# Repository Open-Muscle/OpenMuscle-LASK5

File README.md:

# LASK5 – A Gloveless Smart Glove Controller

LASK5 is a compact, gloveless smart glove controller designed for robotics, machine learning, and human-computer interaction projects. Originally created to assist with labeling movement data for the [OpenMuscle](https://openmuscle.org) project, this controller is now a fully open-source interface capable of controlling robotic hands, LED sculptures, and more.

```markdown
📌 This device is part of the OpenMuscle ecosystem.  
For project-wide documentation, visit the [OpenMuscle Hub](https://github.com/Open-Muscle/OpenMuscle-Hub).
```

---

## 📽️ Watch the Demo

🎥 **YouTube Video:** [LASK5: The Gloveless Smart Glove](https://youtu.be/DJxaf0ww6us)

---

## 🔧 Features

- ESP32-S3 based (Wi-Fi + ESP-NOW enabled)
- 4-piston finger input with hall sensors
- Thumb joystick
- 128x32 OLED display for menus and feedback
- 4 SMD buttons for UI control
- Modular headers for add-ons (gyroscope, additional sensors)
- Written in MicroPython
- 3D-printable enclosure

---

## 🗂️ Repository Structure

### 🛠️ Hardware (KiCad)

You can find all historical and current KiCad hardware designs under:

📂 [`KiCad/`](https://github.com/Open-Muscle/OpenMuscle-LASK5/tree/main/KiCad)

Each folder contains complete KiCad files, BOMs, and version-specific layout changes.

| Version | Description | Folder |
|---------|-------------|--------|
| **v3.0** (Proposed) | New layout with joystick, button updates | [LASK_V3-0](https://github.com/Open-Muscle/OpenMuscle-LASK5/tree/main/KiCad/LASK_V3-0) |
| v2.0 | Button layout revision, early joystick test | [LASK_V2-0](https://github.com/Open-Muscle/OpenMuscle-LASK5/tree/main/KiCad/LASK_V2-0) |
| v1.1 | Original layout with 3-button config | [LASK_V1-1](https://github.com/Open-Muscle/OpenMuscle-LASK5/tree/main/KiCad/LASK_V1-1) |

🧩 Component footprints are stored in:
- [`ESP32WROOMfootprint`](https://github.com/Open-Muscle/OpenMuscle-LASK5/tree/main/KiCad/ESP32WROOMfootprint)
- [`USBfootprint`](https://github.com/Open-Muscle/OpenMuscle-LASK5/tree/main/KiCad/USBfootprint)
- [`ICM-42688-P`](https://github.com/Open-Muscle/OpenMuscle-LASK5/tree/main/KiCad/ICM-42688-P)

---

### 💾 Firmware

The firmware for all LASK versions is maintained centrally in:

📂 [OpenMuscle-Software → `/embedded/lask5`](https://github.com/Open-Muscle/OpenMuscle-Software/tree/main/embedded/LASK5)

> ✅ Be sure to match the firmware branch or directory with your hardware version (see notes in the firmware repo for version compatibility).

---

## 🧠 Use Cases

- Robotic hand control (e.g. HiWonder, Arduino-powered systems)
- LED and kinetic art control
- Machine learning data labeling (OpenMuscle)
- Custom HCI devices, VR/AR control experiments

---

## 🚀 Getting Started

1. Visit the [OpenMuscle Hub](https://github.com/Open-Muscle/OpenMuscle-Hub) for device setup overview.
2. Select your hardware version from the `/KiCad` folder.
3. Follow included assembly instructions (or upcoming guides at [openmuscle.org](https://openmuscle.org)).
4. Flash your ESP32-S3 using the LASK5 firmware from [OpenMuscle-Software](https://github.com/Open-Muscle/OpenMuscle-Software).
5. Power on, test input, and begin using ESP-NOW or serial modes.

---

## 🤝 Contribute

We welcome PRs for hardware, firmware, or documentation.  
You can also submit ideas or questions in [OpenMuscle Discussions](https://github.com/Open-Muscle/OpenMuscle-Hub/discussions) (coming soon).

> If you build your own LASK5 device, let us know!  
> Tag [@OpenMuscle](https://github.com/Open-Muscle) or submit to the Community Builds section.

---

## 📜 License

This repository is covered by a combination of licenses based on content type:

- **Hardware Design Files** (KiCad schematics, PCB layouts, mechanical files):  
  📄 [CERN Open Hardware License v2.0 – Strongly Reciprocal (CERN-OHL-S)](https://ohwr.org/cern_ohl_s_v2.txt)  
  → You may copy, modify, and manufacture hardware as long as you release modifications under the same license.

- **Firmware and Code Snippets** (e.g. MicroPython, setup scripts):  
  📄 [MIT License](https://opensource.org/licenses/MIT)  
  → You may use, modify, and redistribute the code freely with attribution.

- **Art and Visual Media** (e.g. logos, SVGs, diagrams, illustrations):  
  🎨 [Creative Commons Attribution 4.0 International (CC BY 4.0)](https://creativecommons.org/licenses/by/4.0/)  
  → You may use and remix art assets with credit to the original authors.
  
🔍 The hardware license text lives at [LICENSE](LICENSE) (root) and in [LICENSES/](LICENSES/).

---

Made with 💡 by [TURFPTAx](https://github.com/turfptax) for the OpenMuscle initiative.

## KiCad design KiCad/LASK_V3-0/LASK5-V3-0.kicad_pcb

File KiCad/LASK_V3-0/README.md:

# LASK v3 – OpenMuscle Labeler PCB

**Version:** 3.0  
**KiCad Version:** 9.0.1  
**Project Type:** Embedded hardware (ESP32-based controller)  
**Use Case:** Labeling hand movement data for prosthetic machine learning models

This is the third iteration of the LASK (Labeler for Sensor Kit) PCB, designed as part of the OpenMuscle project. LASK v3 is a handheld device used to interact with muscle sensors, label data, and provide haptic and motion feedback during training sessions.

---

## 🧠 Major Additions in v3

- ✅ Added **haptic motor driver** with flyback diode protection  
- ✅ Added **ICM-42688-P IMU** (I²C, with alternate support for SPI)  
- ✅ Enhanced **power management** using a push-button latch and USB auto-power-on  
- ✅ Clean GPIO assignments for consistent firmware development

---

## 🧩 System Overview

| Subsystem           | Description |
|--------------------|-------------|
| **MCU**            | ESP32-S3-WROOM-1 (16MB flash, 8MB PSRAM) |
| **Sensors**        | 4x Hall effect sensors w/ 100nF capacitors to ground |
| **IMU**            | ICM-42688-P (I²C: GPIO8=SDA, GPIO9=SCL) |
| **Display**        | SSD1306 OLED (I²C shared) |
| **Input**          | 2 buttons (Menu & Select), Thumb joystick w/ push |
| **Output**         | Haptic motor driven via MOSFET on GPIO17 |
| **Power**          | MAX16054 latch, TPS7A0333 LDO, LTC4054 charger |
| **Interface**      | USB-C for charging and programming |

---

## 🧷 GPIO Pinout

| Function                | GPIO |
|------------------------|------|
| Hall Sensor 0          | 1    |
| Hall Sensor 1          | 2    |
| Hall Sensor 2          | 3    |
| Hall Sensor 3          | 4    |
| Joystick X             | 5    |
| Joystick Y             | 6    |
| Joystick Switch        | 7    |
| I²C SDA (IMU + OLED)   | 8    |
| I²C SCL (IMU + OLED)   | 9    |
| Select Button          | 10   |
| SPI MISO               | 11   |
| SPI SCK                | 12   |
| SPI MOSI               | 13   |
| Haptic Motor Signal    | 17   |
| Battery Voltage ADC    | 18   |
| Menu Button            | 21   |
| SPI CS (available)     | 22   |

---

## 🔋 Power Management

- **Charging:** LTC4054 linear charger via USB-C  
- **Voltage Regulation:** TPS7A0333 LDO with EN pin control  
- **Power-on Logic:** MAX16054 handles push-button latching  
  - **VBUS detection** auto-enables LDO via diode OR circuit  
  - Power can also be toggled with push button  
- **Haptic Driver:** IRLML2060 N-MOSFET, protected by 1N4007 diode

---

## 🛠️ Schematic

> 📁 Located in `/kicad_project/`

---

## 🧪 Development Notes

- Future version may migrate IMU to SPI for better performance
- USB VBUS is sensed to allow automatic boot when plugged in
- Add decoupling capacitors on IMU pins for improved stability (see TODO in schematic)

---

## 📂 Repository Structure

```
/
├── kicad_project/
│ ├── LASKS-V3_0.kicad_sch
│ └── LASKS-V3_0.kicad_pcb
├── docs/
│ └── lask_v3_schematic.png
├── README.md
```

---

## 🔓 License

Open-source under [CERN-OHL-W v2](https://ohwr.org/project/cernohl/wikis/CERN-OHL-version-2)  
Part of the [OpenMuscle Project](https://openmuscle.org)

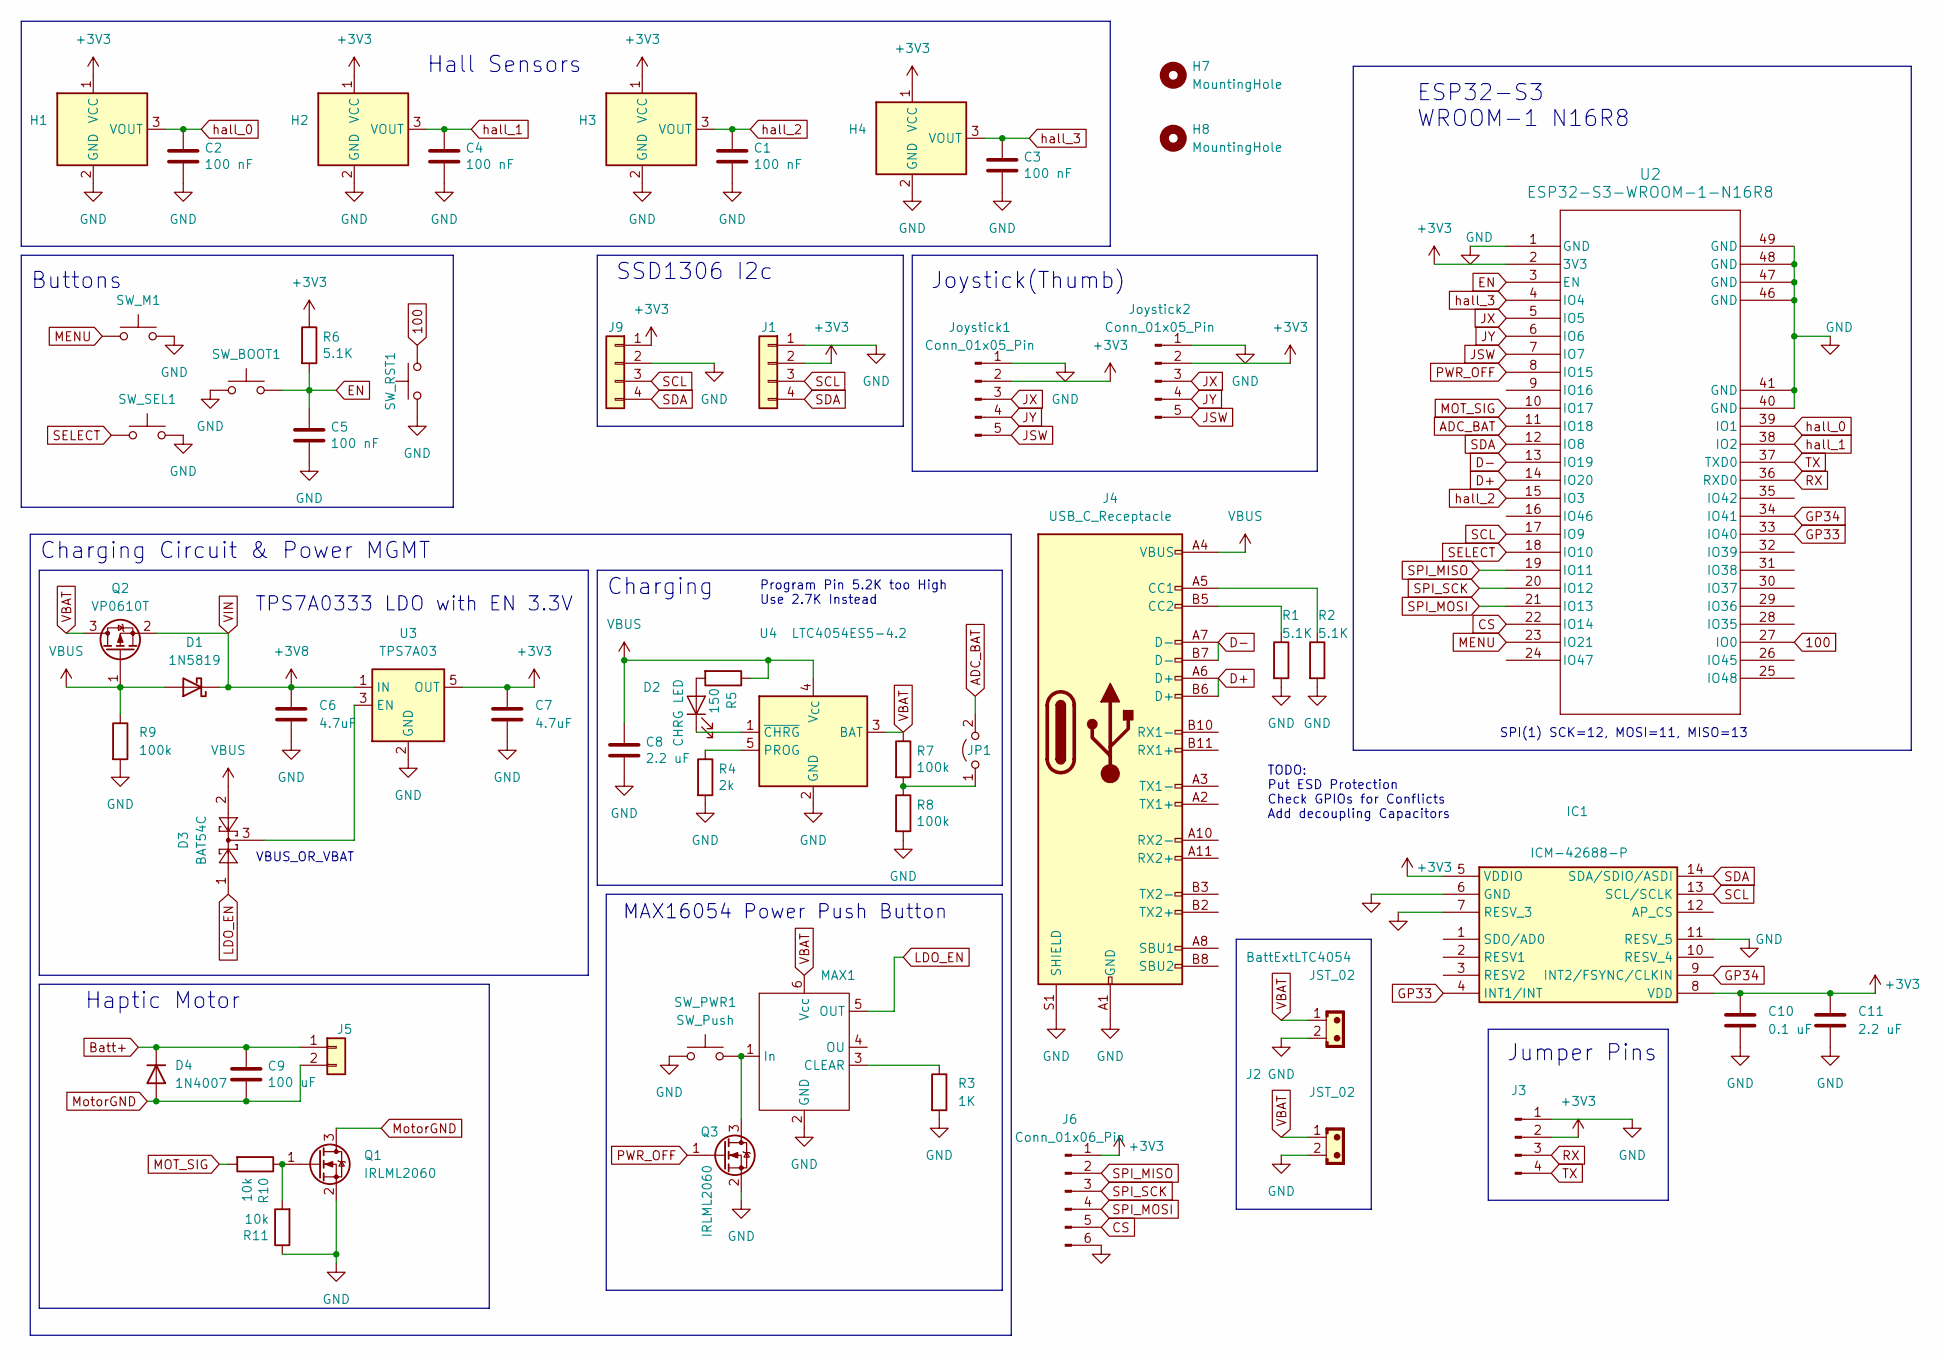
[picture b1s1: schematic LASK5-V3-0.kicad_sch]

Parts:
BattExtLTC4054: JST_02; JST_EH_B2B-EH-A_1x02_P2.50mm_Vertical
C1, C2, C3, C4, C5: 100 nF; C_0603_1608Metric; JLCPN C1525
C6, C7: 4.7uF; C_0805_2012Metric
C8: 2.2 uF; C_0603_1608Metric; JLCPN C12530
C9: 100 uF; C_0603_1608Metric; JLCPN C12530
C10: 0.1 uF; C_0603_1608Metric
C11: 2.2 uF; C_0603_1608Metric
D1: 1N5819; D_SOD-123F
D2: CHRG LED; LED_0805_2012Metric; JLCPN C72043
D3: BAT54C; SOT-23
D4: 1N4007; D_SOD-123
H1, H2, H3, H4: A1369xUA-10; PinHeader_1x03_P2.00mm_Vertical
H7, H8: MountingHole; MountingHole_2.2mm_M2
IC1: ICM-42688-P; IIM42352; Mouser Part Number 410-ICM-42688-P
J1, J9: Conn_01x04; PinHeader_1x04_P2.54mm_Vertical
J2: JST_02; JST_EH_B2B-EH-A_1x02_P2.50mm_Vertical
J3: Conn_01x04_Pin; PinHeader_1x04_P2.00mm_Vertical
J4: USB_C_Receptacle; USB_C_Receptacle_HRO_TYPE-C-31-M-12
J5: Conn_01x02; PinHeader_1x02_P2.00mm_Vertical
J6: Conn_01x06_Pin; PinHeader_1x06_P1.27mm_Vertical
JP1: Jumper_2_Open; SolderJumper-2_P1.3mm_Open_TrianglePad1.0x1.5mm
Joystick1, Joystick2: Conn_01x05_Pin; PinHeader_1x05_P2.00mm_Vertical
MAX1: SOT-23-6
Q1, Q3: IRLML2060; SOT-23
Q2: VP0610T; SOT-23
R1, R2, R6: 5.1K; R_0603_1608Metric; JLCPN C25905
R3: 1K; R_0603_1608Metric
R4: 2k; R_0603_1608Metric; JLCPN C25905
R5: 150; R_0603_1608Metric; JLCPN C4109
R7, R8: 100k; R_0603_1608Metric; JLCPN C25905
R9: 100k; R_0603_1608Metric
R10, R11: 10k; R_0603_1608Metric; JLCPN C25744
SW_BOOT1: SW_Push; EVQP2P02M
SW_M1: SW_Push; EVQP2P02M
SW_PWR1: SW_Push; EVQP2P02M
SW_RST1: SW_Push; EVQP2P02M
SW_SEL1: SW_Push; EVQP2P02M
U2: ESP32-S3-WROOM-1-N16R8; ESP32-S3-WROOM-1_EXP
U3: TPS7A03; SOT-23-5
U4: LTC4054ES5-4.2; TSOT-23-5

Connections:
100: SW_RST1.2, U2.27 (IO0)
+3V3: C7.1, C10.1, C11.1, H1.1 (VCC), H2.1 (VCC), H3.1 (VCC), H4.1 (VCC), IC1.5 (VDDIO), IC1.8 (VDD), J1.2, J3.2, J6.1, J9.1, Joystick1.2, Joystick2.2, R6.1, U2.2 (3V3), U3.5 (OUT)
ADC_BAT: JP1.2 (B), U2.11 (IO18)
Batt+: C9.2, D4.1 (K), J5.1
CS: J6.5, U2.22 (IO14)
D+: J4.A6 (D+), J4.B6 (D+), U2.14 (IO20)
D-: J4.A7 (D-), J4.B7 (D-), U2.13 (IO19)
EN: C5.2, R6.2, SW_BOOT1.2, U2.3 (EN)
GND: BattExtLTC4054.2, C1.1, C2.1, C3.1, C4.1, C5.1, C6.2, C7.2, C8.1, C10.2, C11.2, H1.2 (GND), H2.2 (GND), H3.2 (GND), H4.2 (GND), IC1.6 (GND), IC1.7 (RESV_3), IC1.11 (RESV_5), J1.1, J2.2, J3.1, J4.A1 (GND), J4.A12 (GND), J4.B1 (GND), J4.B12 (GND), J4.S1 (SHIELD), J6.6, J9.2, Joystick1.1, Joystick2.1, MAX1.2 (GND), Q1.2 (S), Q3.2 (S), R1.2, R2.2, R3.2, R4.2, R8.2, R9.2, R11.1, SW_BOOT1.1, SW_M1.2, SW_PWR1.1, SW_RST1.1, SW_SEL1.2, U2.1 (GND), U2.40 (GND), U2.41 (GND), U2.46 (GND), U2.47 (GND), U2.48 (GND), U2.49 (GND), U3.2 (GND), U4.2 (GND)
GP33: IC1.4 (INT1/INT), U2.33 (IO40)
GP34: IC1.9 (INT2/FSYNC/CLKIN), U2.34 (IO41)
JSW: Joystick1.5, Joystick2.5, U2.7 (IO7)
JX: Joystick1.3, Joystick2.3, U2.5 (IO5)
JY: Joystick1.4, Joystick2.4, U2.6 (IO6)
LDO_EN: D3.1, MAX1.5 (OUT)
MENU: SW_M1.1, U2.23 (IO21)
MOT_SIG: R10.2, U2.10 (IO17)
MotorGND: C9.1, D4.2 (A), J5.2, Q1.3 (D)
unnamed: D2.2 (A), R5.2
unnamed: D2.1 (K), U4.1 (~CHRG)
unnamed: J4.A5 (CC1), R2.1
unnamed: J4.B5 (CC2), R1.1
unnamed: JP1.1 (A), R7.2, R8.1
unnamed: MAX1.3 (CLEAR), R3.1
unnamed: MAX1.1 (In), Q3.3 (D), SW_PWR1.2
unnamed: Q1.1 (G), R10.1, R11.2
unnamed: D3.3, U3.3 (EN)
unnamed: R4.1, U4.5 (PROG)
PWR_OFF: Q3.1 (G), U2.8 (IO15)
RX: J3.3, U2.36 (RXD0)
SCL: IC1.13 (SCL/SCLK), J1.3, J9.3, U2.17 (IO9)
SDA: IC1.14 (SDA/SDIO/ASDI), J1.4, J9.4, U2.12 (IO8)
SELECT: SW_SEL1.1, U2.18 (IO10)
SPI_MISO: J6.2, U2.19 (IO11)
SPI_MOSI: J6.4, U2.21 (IO13)
SPI_SCK: J6.3, U2.20 (IO12)
TX: J3.4, U2.37 (TXD0)
VBAT: BattExtLTC4054.1, J2.1, MAX1.6 (Vcc), Q2.3 (D), R7.1, U4.3 (BAT)
VBUS: C8.2, D1.2 (A), D3.2, J4.A4 (VBUS), J4.A9 (VBUS), J4.B4 (VBUS), J4.B9 (VBUS), Q2.1 (G), R5.1, R9.1, U4.4 (V_{CC})
VIN: C6.1, D1.1 (K), Q2.2 (S), U3.1 (IN)
hall_0: C2.2, H1.3 (VOUT), U2.39 (IO1)
hall_1: C4.2, H2.3 (VOUT), U2.38 (IO2)
hall_2: C1.2, H3.3 (VOUT), U2.15 (IO3)
hall_3: C3.2, H4.3 (VOUT), U2.4 (IO4)

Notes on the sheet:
Jumper Pins
SPI(1) SCK=12, MOSI=11, MISO=13
Buttons
MAX16054 Power Push Button
Joystick(Thumb)
Program Pin 5.2K too High Use 2.7K Instead
Charging
ESP32-S3 WROOM-1 N16R8
Charging Circuit & Power MGMT
SSD1306 I2c
TODO: Put ESD Protection Check GPIOs for Conflicts Add decoupling Capacitors
TPS7A0333 LDO with EN 3.3V
Hall Sensors
VBUS_OR_VBAT
Haptic Motor

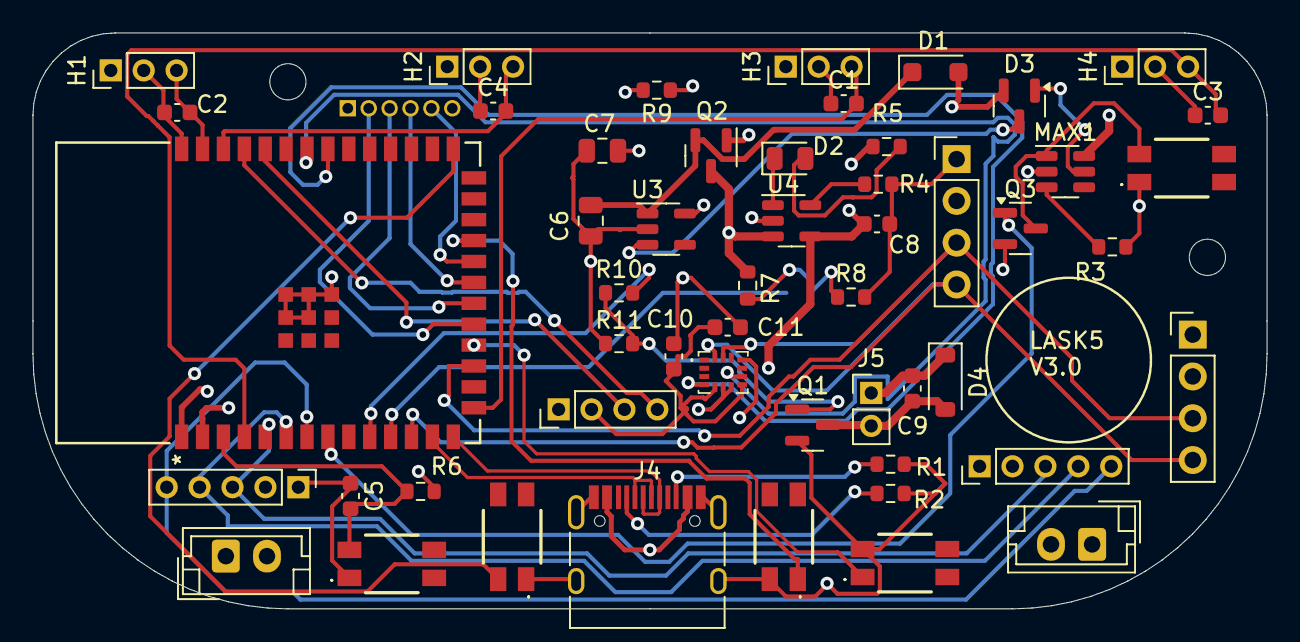
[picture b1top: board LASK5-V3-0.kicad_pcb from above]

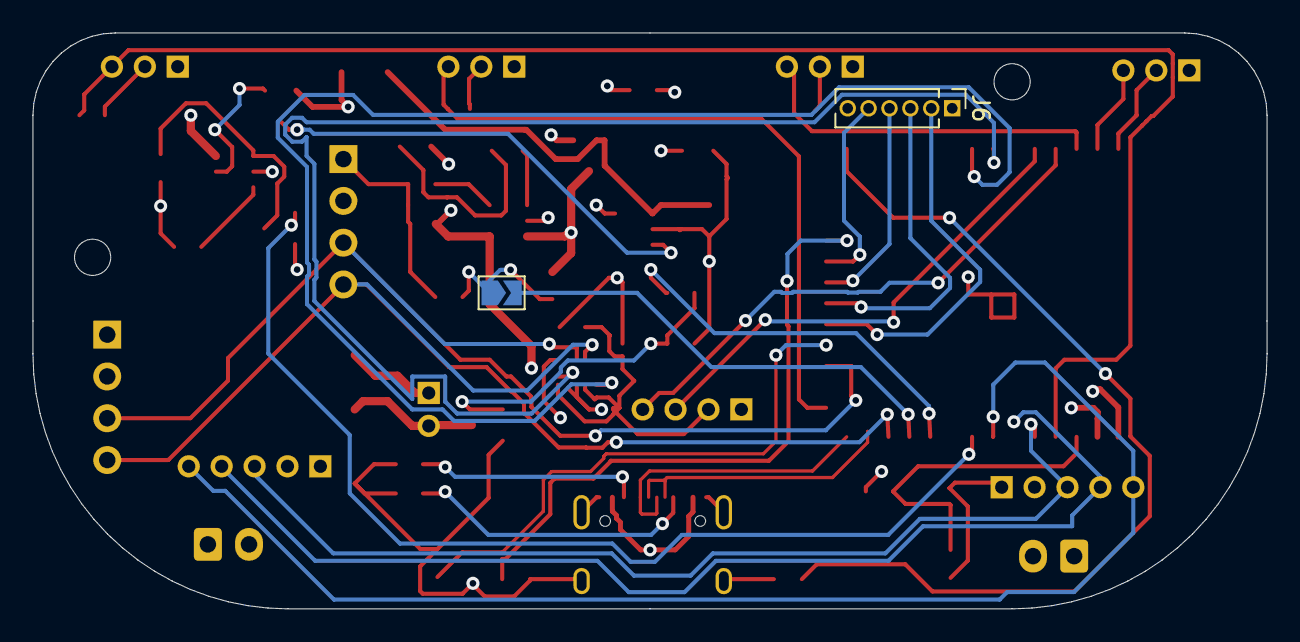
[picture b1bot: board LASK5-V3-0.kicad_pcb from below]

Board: 4 copper layers, 75.0 x 35.0 mm, 56 parts (2 on the bottom side), 44 nets.

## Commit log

2025-05-19 Base Files
2025-05-19 BOMs
2025-05-24 LASK_V3
2026-02-10 Add V3 schematic, backups; fix firmware path
    Add two KiCad backup ZIPs for LASK5 V3, add a JPG schematic (Open Muscle Labeler (LASK5) Schematic-V3.jpg), and update the existing PDF schematic. Also correct the README firmware link path to point 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
2026-05-28 Update LASK5 V3 schematic and PCB; add design backups
2026-05-28 Add .gitignore for KiCad lock/autosave files
2026-06-09 Add root CERN-OHL-S-2.0 LICENSE; fix license badge and link
    Root LICENSE file so GitHub detects the hardware license. Replace the
    misleading MIT-only badge with hardware/code badges and point the license
    section at the real files instead of a nonexistent ../LICENSE.md.

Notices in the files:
README.md:
Hardware: CERN-OHL-S-2.0
